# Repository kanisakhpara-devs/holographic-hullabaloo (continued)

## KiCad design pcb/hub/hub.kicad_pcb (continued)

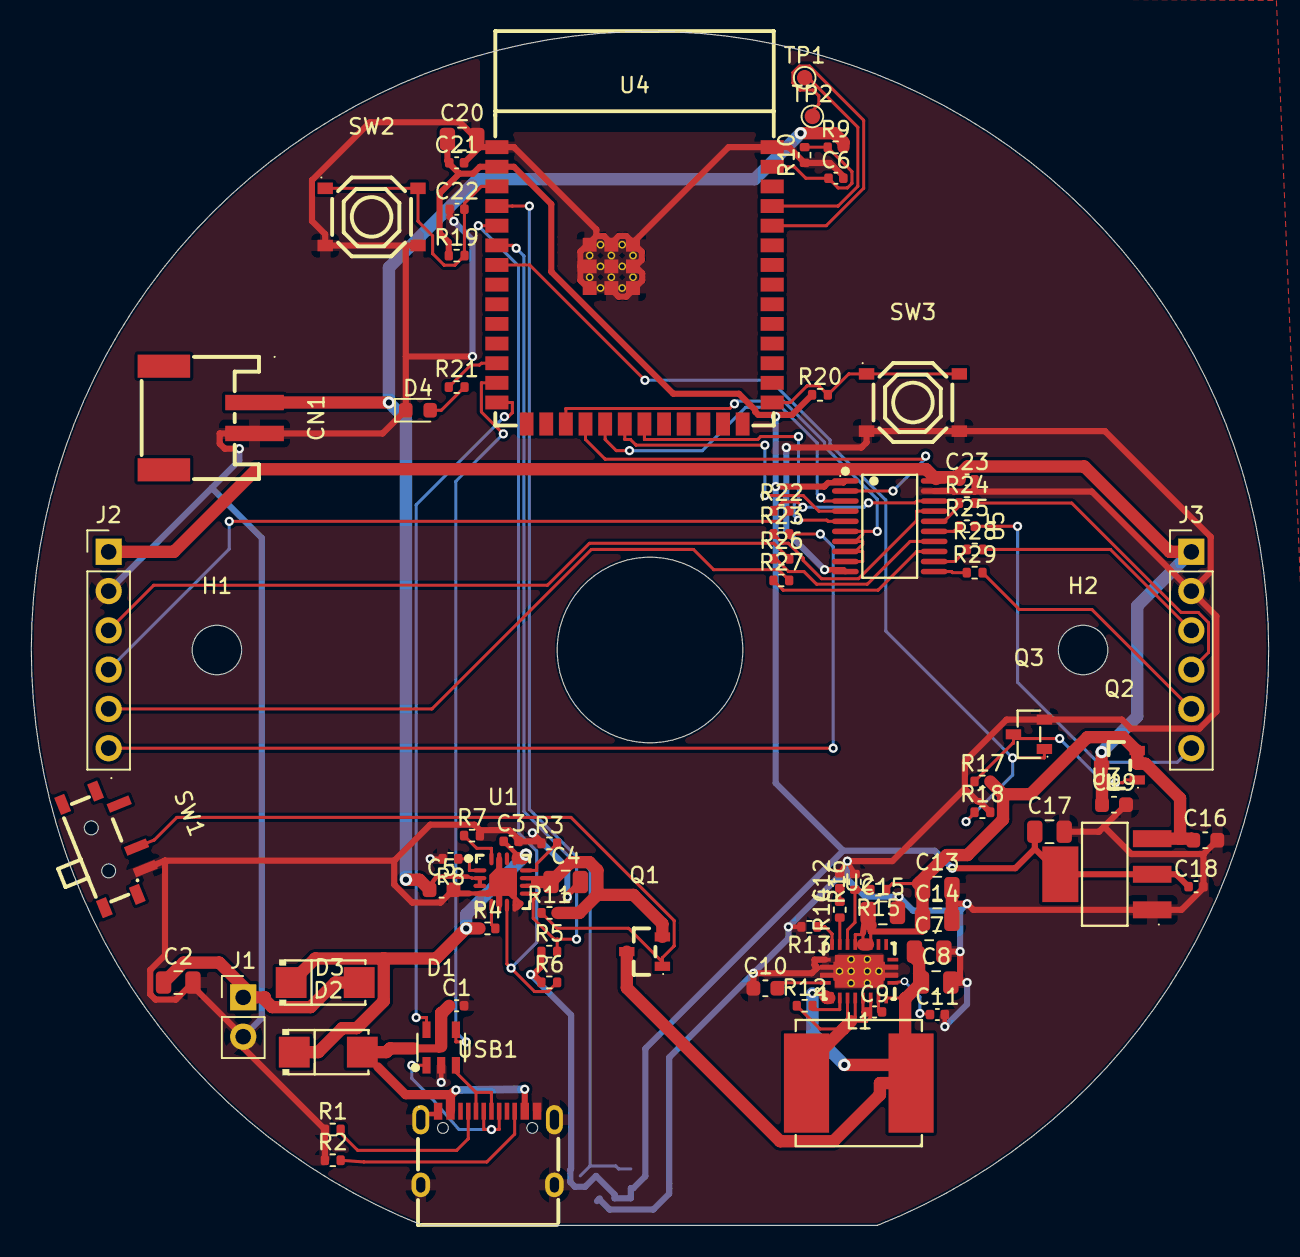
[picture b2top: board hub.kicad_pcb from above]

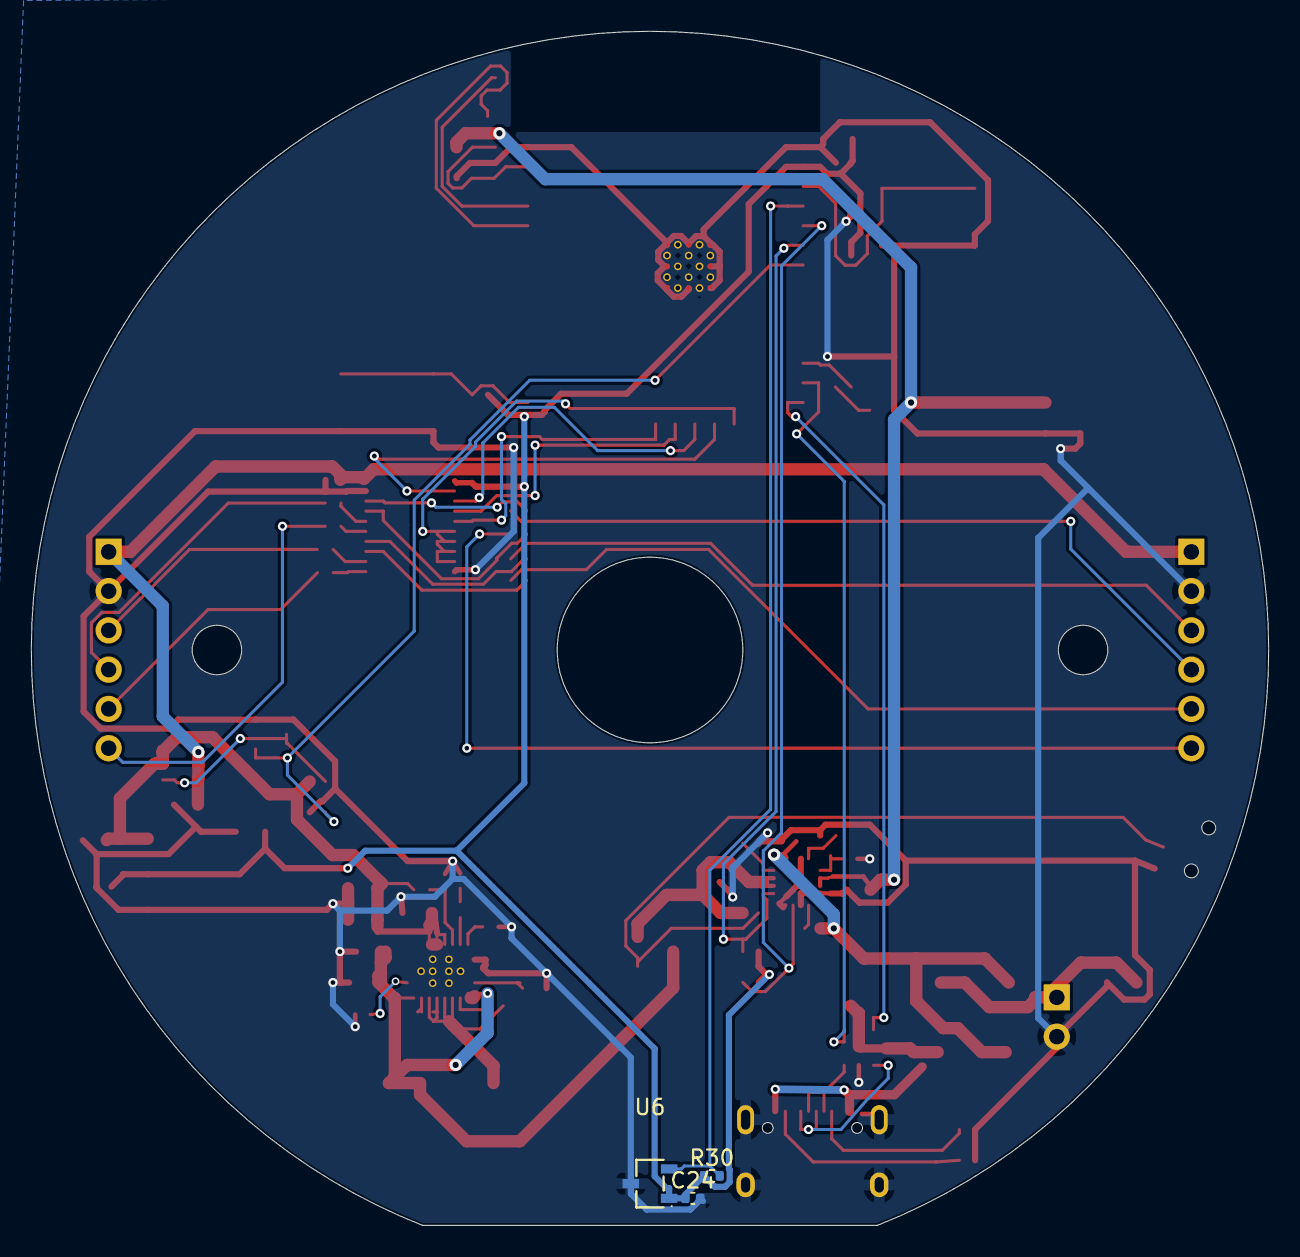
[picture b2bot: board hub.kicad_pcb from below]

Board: 2 copper layers, 80.0 x 77.2 mm, 80 parts (3 on the bottom side), 63 nets.

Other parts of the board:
H1, H2: MountingHole_3.2mm_M3

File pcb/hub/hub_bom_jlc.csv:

"Comment","Designator","Footprint","LCSC Part #"
"100nF","C1,C6,C9,C11,C18,C21,C23,C24","Capacitor_SMD:C_0402_1005Metric","C1525"
"22uF","C2,C4,C7,C8,C13,C14,C15,C17,C20","Capacitor_SMD:C_0805_2012Metric","C45783"
"1uF","C3,C22","Capacitor_SMD:C_0402_1005Metric","C52923"
"10uF","C5,C10,C16,C19","Capacitor_SMD:C_0603_1608Metric","C19702"
"10nF","C12","Capacitor_SMD:C_0402_1005Metric","C15195"
"S2B-PH-SM4-TB","CN1","fallen:CONN-SMD_P2.00_S2B-PH-SM4-TB-LF-SN","C295747"
"USBLC6-2SC6","D1","fallen:SOT-23-6_L2.9-W1.6-P0.95-LS2.8-BL","C7519"
"SS34_C8678","D2,D3","fallen:SMA_L4.3-W2.6-LS5.2-RD","C8678"
"LED","D4","LED_SMD:LED_0603_1608Metric","C2286"
"Conn_01x02","J1","Connector_PinHeader_2.54mm:PinHeader_1x02_P2.54mm_Vertical",""
"Conn_01x06","J2,J3","Connector_PinHeader_2.54mm:PinHeader_1x06_P2.54mm_Vertical",""
"SWPA8040S2R2MT","L1","fallen:IND-SMD_L8.0-W8.0_SWPA8040S","C36415"
"AO3401A","Q1,Q2","fallen:SOT-23_L2.9-W1.3-P1.90-LS2.4-BR","C15127"
"2N7002","Q3","fallen:SOT-23-3_L2.9-W1.3-P1.90-LS2.4-BR","C8545"
"5.1k","R1,R2","Resistor_SMD:R_0402_1005Metric","C25905"
"1.1k","R3","Resistor_SMD:R_0402_1005Metric","C482070"
"100k","R4,R9,R10,R11,R16,R17,R18","Resistor_SMD:R_0402_1005Metric","C25741"
"10k","R5,R6,R8,R14,R19,R20,R30","Resistor_SMD:R_0402_1005Metric","C25744"
"1.18k","R7","Resistor_SMD:R_0402_1005Metric","C2092244"
"330k","R12","Resistor_SMD:R_0402_1005Metric","C102977"
"267k","R13","Resistor_SMD:R_0402_1005Metric","C2998050"
"316k","R15","Resistor_SMD:R_0402_1005Metric","C25777"
"1k","R21","Resistor_SMD:R_0402_1005Metric","C11702"
"33","R22,R23,R24,R25,R26,R27,R28,R29","Resistor_SMD:R_0402_1005Metric","C25105"
"MSK12C02","SW1","fallen:SW-TH_MSK12C02","C431540"
"TS-1187A-B-A-B","SW2,SW3","fallen:SW-SMD_4P-L5.1-W5.1-P3.70-LS6.5-TL_H1.5","C318884"
"TestPoint","TP1,TP2","TestPoint:TestPoint_Pad_D1.0mm",""
"BQ24073RGTR","U1","fallen:QFN-16_L3.0-W3.0-P0.50-TL-EP1.7","C15220"
"TPS61088RHLR","U2","fallen:VQFN-20_L4.6-W3.6-P0.50-BL","C87357"
"AMS1117-3.3","U3","fallen:SOT-223-3_L6.5-W3.4-P2.30-LS7.0-BR","C6186"
"ESP32-S3-WROOM-1-N8","U4","fallen:WIFIM-SMD_ESP32-S3-WROOM-1-N8","C2913198"
"74AHCT245APWJ","U5","fallen:TSSOP-20_L6.5-W4.4-P0.65-LS6.4-BL","C554610"
"DRV5023FAQDBZR","U6","fallen:SOT-23-3_L2.9-W1.6-P1.90-LS2.8-BR","C114983"
"TYPE-C 16PIN 2MD","USB1","fallen:USB-C-SMD_TYPE-C-16PIN-2MD-073","C2765186"

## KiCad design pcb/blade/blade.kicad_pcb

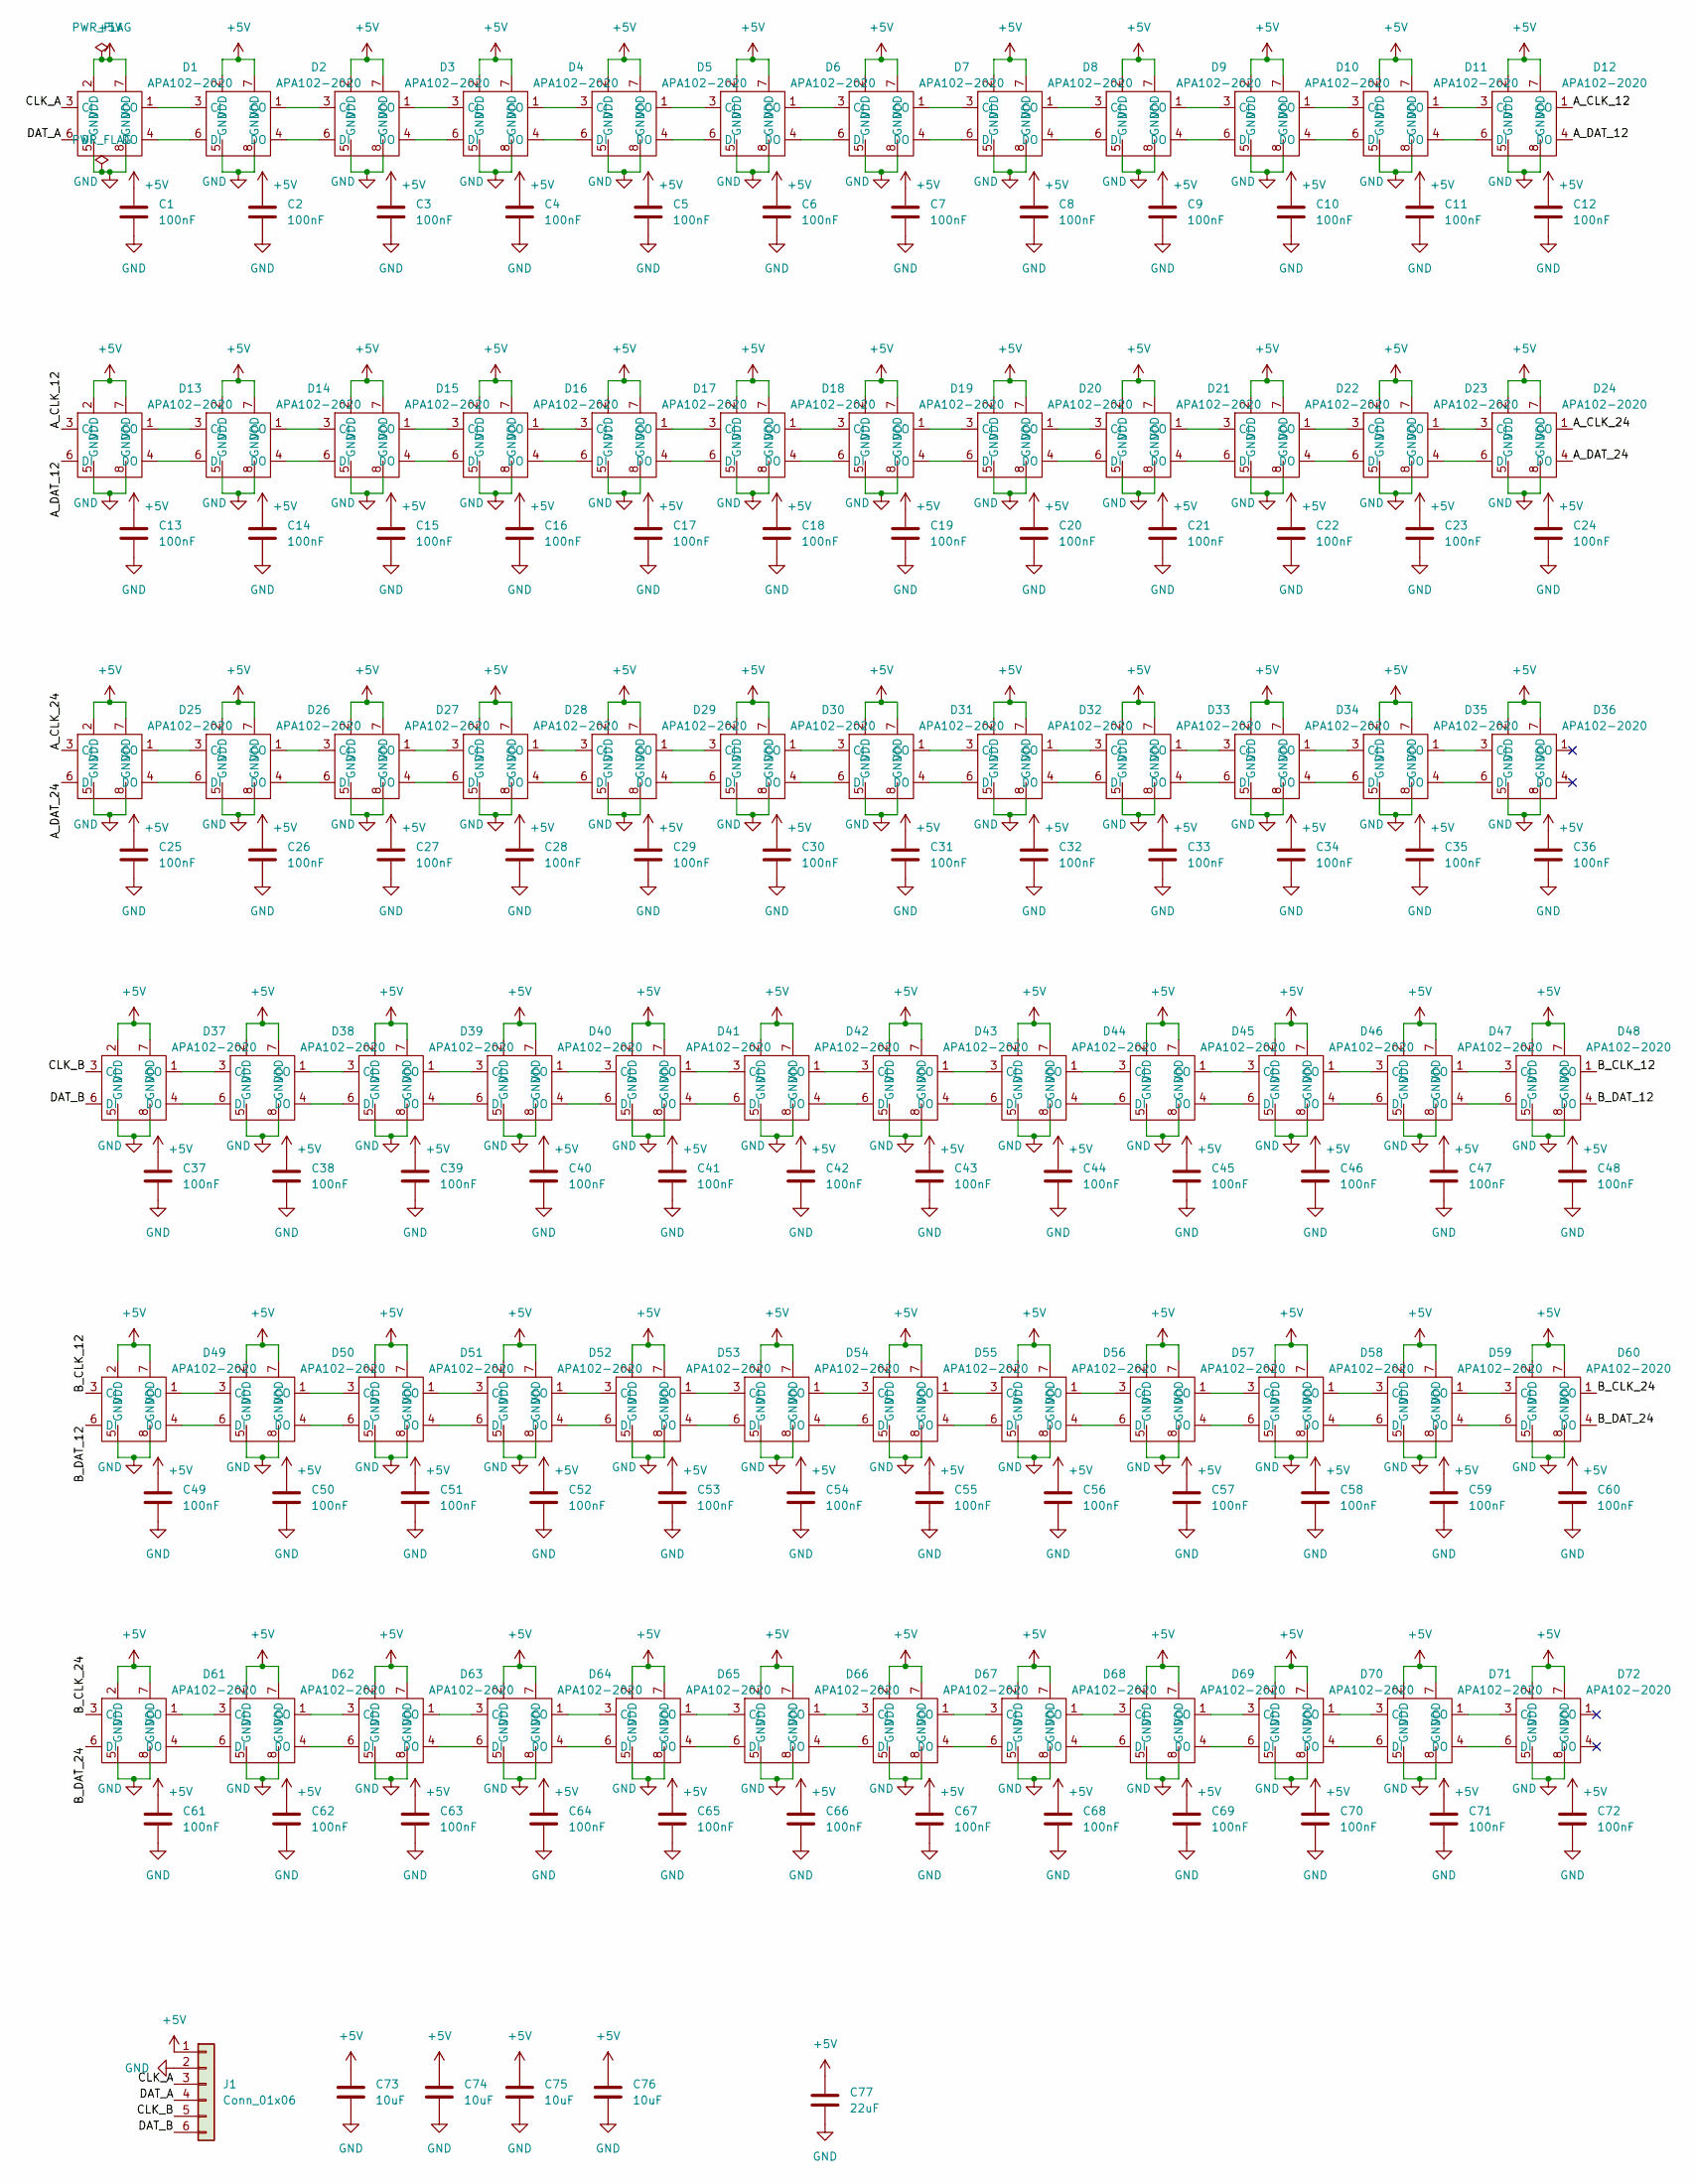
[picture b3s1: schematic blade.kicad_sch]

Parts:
C1, C2, C3, C4, C5, C6, C7, C8, C9, C10, C11, C12, C13, C14, C15, C16, C17, C18, C19, C20, C21, C22, C23, C24, C25, C26, C27, C28, C29, C30, C31, C32, C33, C34, C35, C36, C37, C38, C39, C40, C41, C42, C43, C44, C45, C46, C47, C48, C49, C50, C51, C52, C53, C54, C55, C56, C57, C58, C59, C60, C61, C62, C63, C64, C65, C66, C67, C68, C69, C70, C71, C72: 100nF; C_0402_1005Metric
C73, C74, C75, C76: 10uF; C_0603_1608Metric
C77: 22uF; C_0603_1608Metric
D1, D2, D3, D4, D5, D6, D7, D8, D9, D10, D11, D12, D13, D14, D15, D16, D17, D18, D19, D20, D21, D22, D23, D24, D25, D26, D27, D28, D29, D30, D31, D32, D33, D34, D35, D36, D37, D38, D39, D40, D41, D42, D43, D44, D45, D46, D47, D48, D49, D50, D51, D52, D53, D54, D55, D56, D57, D58, D59, D60, D61, D62, D63, D64, D65, D66, D67, D68, D69, D70, D71, D72: APA102-2020
J1: Conn_01x06; PinHeader_2x03_P2.54mm_Vertical

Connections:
+5V: C1.1, C2.1, C3.1, C4.1, C5.1, C6.1, C7.1, C8.1, C9.1, C10.1, C11.1, C12.1, C13.1, C14.1, C15.1, C16.1, C17.1, C18.1, C19.1, C20.1, C21.1, C22.1, C23.1, C24.1, C25.1, C26.1, C27.1, C28.1, C29.1, C30.1, C31.1, C32.1, C33.1, C34.1, C35.1, C36.1, C37.1, C38.1, C39.1, C40.1, C41.1, C42.1, C43.1, C44.1, C45.1, C46.1, C47.1, C48.1, C49.1, C50.1, C51.1, C52.1, C53.1, C54.1, C55.1, C56.1, C57.1, C58.1, C59.1, C60.1, C61.1, C62.1, C63.1, C64.1, C65.1, C66.1, C67.1, C68.1, C69.1, C70.1, C71.1, C72.1, C73.1, C74.1, C75.1, C76.1, C77.1, D1.2 (VDD), D1.7 (VDD), D2.2 (VDD), D2.7 (VDD), D3.2 (VDD), D3.7 (VDD), D4.2 (VDD), D4.7 (VDD), D5.2 (VDD), D5.7 (VDD), D6.2 (VDD), D6.7 (VDD), D7.2 (VDD), D7.7 (VDD), D8.2 (VDD), D8.7 (VDD), D9.2 (VDD), D9.7 (VDD), D10.2 (VDD), D10.7 (VDD), D11.2 (VDD), D11.7 (VDD), D12.2 (VDD), D12.7 (VDD), D13.2 (VDD), D13.7 (VDD), D14.2 (VDD), D14.7 (VDD), D15.2 (VDD), D15.7 (VDD), D16.2 (VDD), D16.7 (VDD), D17.2 (VDD), D17.7 (VDD), D18.2 (VDD), D18.7 (VDD), D19.2 (VDD), D19.7 (VDD), D20.2 (VDD), D20.7 (VDD), D21.2 (VDD), D21.7 (VDD), D22.2 (VDD), D22.7 (VDD), D23.2 (VDD), D23.7 (VDD), D24.2 (VDD), D24.7 (VDD), D25.2 (VDD), D25.7 (VDD), D26.2 (VDD), D26.7 (VDD), D27.2 (VDD), D27.7 (VDD), D28.2 (VDD), D28.7 (VDD), D29.2 (VDD), D29.7 (VDD), D30.2 (VDD), D30.7 (VDD), D31.2 (VDD), D31.7 (VDD), D32.2 (VDD), D32.7 (VDD), D33.2 (VDD), D33.7 (VDD), D34.2 (VDD), D34.7 (VDD), D35.2 (VDD), D35.7 (VDD), D36.2 (VDD), D36.7 (VDD), D37.2 (VDD), D37.7 (VDD), D38.2 (VDD), D38.7 (VDD), D39.2 (VDD), D39.7 (VDD), D40.2 (VDD), D40.7 (VDD), D41.2 (VDD), D41.7 (VDD), D42.2 (VDD), D42.7 (VDD), D43.2 (VDD), D43.7 (VDD), D44.2 (VDD), D44.7 (VDD), D45.2 (VDD), D45.7 (VDD), D46.2 (VDD), D46.7 (VDD), D47.2 (VDD), D47.7 (VDD), D48.2 (VDD), D48.7 (VDD), D49.2 (VDD), D49.7 (VDD), D50.2 (VDD), D50.7 (VDD), D51.2 (VDD), D51.7 (VDD), D52.2 (VDD), D52.7 (VDD), D53.2 (VDD), D53.7 (VDD), D54.2 (VDD), D54.7 (VDD), D55.2 (VDD), D55.7 (VDD), D56.2 (VDD), D56.7 (VDD), D57.2 (VDD), D57.7 (VDD), D58.2 (VDD), D58.7 (VDD), D59.2 (VDD), D59.7 (VDD), D60.2 (VDD), D60.7 (VDD), D61.2 (VDD), D61.7 (VDD), D62.2 (VDD), D62.7 (VDD), D63.2 (VDD), D63.7 (VDD), D64.2 (VDD), D64.7 (VDD), D65.2 (VDD), D65.7 (VDD), D66.2 (VDD), D66.7 (VDD), D67.2 (VDD), D67.7 (VDD), D68.2 (VDD), D68.7 (VDD), D69.2 (VDD), D69.7 (VDD), D70.2 (VDD), D70.7 (VDD), D71.2 (VDD), D71.7 (VDD), D72.2 (VDD), D72.7 (VDD), J1.1
/A_CLK_12: D12.1 (CO), D13.3 (CI)
/A_CLK_24: D24.1 (CO), D25.3 (CI)
/A_DAT_12: D12.4 (DO), D13.6 (DI)
/A_DAT_24: D24.4 (DO), D25.6 (DI)
/B_CLK_12: D48.1 (CO), D49.3 (CI)
/B_CLK_24: D60.1 (CO), D61.3 (CI)
/B_DAT_12: D48.4 (DO), D49.6 (DI)
/B_DAT_24: D60.4 (DO), D61.6 (DI)
/CLK_A: D1.3 (CI), J1.3
/CLK_B: D37.3 (CI), J1.5
/DAT_A: D1.6 (DI), J1.4
/DAT_B: D37.6 (DI), J1.6
GND: C1.2, C2.2, C3.2, C4.2, C5.2, C6.2, C7.2, C8.2, C9.2, C10.2, C11.2, C12.2, C13.2, C14.2, C15.2, C16.2, C17.2, C18.2, C19.2, C20.2, C21.2, C22.2, C23.2, C24.2, C25.2, C26.2, C27.2, C28.2, C29.2, C30.2, C31.2, C32.2, C33.2, C34.2, C35.2, C36.2, C37.2, C38.2, C39.2, C40.2, C41.2, C42.2, C43.2, C44.2, C45.2, C46.2, C47.2, C48.2, C49.2, C50.2, C51.2, C52.2, C53.2, C54.2, C55.2, C56.2, C57.2, C58.2, C59.2, C60.2, C61.2, C62.2, C63.2, C64.2, C65.2, C66.2, C67.2, C68.2, C69.2, C70.2, C71.2, C72.2, C73.2, C74.2, C75.2, C76.2, C77.2, D1.5 (GND), D1.8 (GND), D2.5 (GND), D2.8 (GND), D3.5 (GND), D3.8 (GND), D4.5 (GND), D4.8 (GND), D5.5 (GND), D5.8 (GND), D6.5 (GND), D6.8 (GND), D7.5 (GND), D7.8 (GND), D8.5 (GND), D8.8 (GND), D9.5 (GND), D9.8 (GND), D10.5 (GND), D10.8 (GND), D11.5 (GND), D11.8 (GND), D12.5 (GND), D12.8 (GND), D13.5 (GND), D13.8 (GND), D14.5 (GND), D14.8 (GND), D15.5 (GND), D15.8 (GND), D16.5 (GND), D16.8 (GND), D17.5 (GND), D17.8 (GND), D18.5 (GND), D18.8 (GND), D19.5 (GND), D19.8 (GND), D20.5 (GND), D20.8 (GND), D21.5 (GND), D21.8 (GND), D22.5 (GND), D22.8 (GND), D23.5 (GND), D23.8 (GND), D24.5 (GND), D24.8 (GND), D25.5 (GND), D25.8 (GND), D26.5 (GND), D26.8 (GND), D27.5 (GND), D27.8 (GND), D28.5 (GND), D28.8 (GND), D29.5 (GND), D29.8 (GND), D30.5 (GND), D30.8 (GND), D31.5 (GND), D31.8 (GND), D32.5 (GND), D32.8 (GND), D33.5 (GND), D33.8 (GND), D34.5 (GND), D34.8 (GND), D35.5 (GND), D35.8 (GND), D36.5 (GND), D36.8 (GND), D37.5 (GND), D37.8 (GND), D38.5 (GND), D38.8 (GND), D39.5 (GND), D39.8 (GND), D40.5 (GND), D40.8 (GND), D41.5 (GND), D41.8 (GND), D42.5 (GND), D42.8 (GND), D43.5 (GND), D43.8 (GND), D44.5 (GND), D44.8 (GND), D45.5 (GND), D45.8 (GND), D46.5 (GND), D46.8 (GND), D47.5 (GND), D47.8 (GND), D48.5 (GND), D48.8 (GND), D49.5 (GND), D49.8 (GND), D50.5 (GND), D50.8 (GND), D51.5 (GND), D51.8 (GND), D52.5 (GND), D52.8 (GND), D53.5 (GND), D53.8 (GND), D54.5 (GND), D54.8 (GND), D55.5 (GND), D55.8 (GND), D56.5 (GND), D56.8 (GND), D57.5 (GND), D57.8 (GND), D58.5 (GND), D58.8 (GND), D59.5 (GND), D59.8 (GND), D60.5 (GND), D60.8 (GND), D61.5 (GND), D61.8 (GND), D62.5 (GND), D62.8 (GND), D63.5 (GND), D63.8 (GND), D64.5 (GND), D64.8 (GND), D65.5 (GND), D65.8 (GND), D66.5 (GND), D66.8 (GND), D67.5 (GND), D67.8 (GND), D68.5 (GND), D68.8 (GND), D69.5 (GND), D69.8 (GND), D70.5 (GND), D70.8 (GND), D71.5 (GND), D71.8 (GND), D72.5 (GND), D72.8 (GND), J1.2
unnamed: D1.1 (CO), D2.3 (CI)
unnamed: D1.4 (DO), D2.6 (DI)
unnamed: D2.1 (CO), D3.3 (CI)
unnamed: D2.4 (DO), D3.6 (DI)
unnamed: D3.1 (CO), D4.3 (CI)
unnamed: D3.4 (DO), D4.6 (DI)
unnamed: D4.1 (CO), D5.3 (CI)
unnamed: D4.4 (DO), D5.6 (DI)
unnamed: D5.1 (CO), D6.3 (CI)
unnamed: D5.4 (DO), D6.6 (DI)
unnamed: D6.1 (CO), D7.3 (CI)
unnamed: D6.4 (DO), D7.6 (DI)
unnamed: D7.1 (CO), D8.3 (CI)
unnamed: D7.4 (DO), D8.6 (DI)
unnamed: D8.1 (CO), D9.3 (CI)
unnamed: D8.4 (DO), D9.6 (DI)
unnamed: D9.1 (CO), D10.3 (CI)
unnamed: D10.1 (CO), D11.3 (CI)
unnamed: D9.4 (DO), D10.6 (DI)
unnamed: D10.4 (DO), D11.6 (DI)
unnamed: D11.1 (CO), D12.3 (CI)
unnamed: D11.4 (DO), D12.6 (DI)
unnamed: D13.1 (CO), D14.3 (CI)
unnamed: D13.4 (DO), D14.6 (DI)
unnamed: D14.1 (CO), D15.3 (CI)
unnamed: D14.4 (DO), D15.6 (DI)
unnamed: D15.1 (CO), D16.3 (CI)
unnamed: D15.4 (DO), D16.6 (DI)
unnamed: D16.1 (CO), D17.3 (CI)
unnamed: D16.4 (DO), D17.6 (DI)
unnamed: D17.1 (CO), D18.3 (CI)
unnamed: D17.4 (DO), D18.6 (DI)
unnamed: D18.1 (CO), D19.3 (CI)
unnamed: D18.4 (DO), D19.6 (DI)
unnamed: D19.1 (CO), D20.3 (CI)
unnamed: D19.4 (DO), D20.6 (DI)
unnamed: D20.1 (CO), D21.3 (CI)
unnamed: D20.4 (DO), D21.6 (DI)
unnamed: D21.1 (CO), D22.3 (CI)
unnamed: D21.4 (DO), D22.6 (DI)
unnamed: D22.1 (CO), D23.3 (CI)
unnamed: D22.4 (DO), D23.6 (DI)
unnamed: D23.1 (CO), D24.3 (CI)
unnamed: D23.4 (DO), D24.6 (DI)
unnamed: D25.1 (CO), D26.3 (CI)
unnamed: D25.4 (DO), D26.6 (DI)
unnamed: D26.1 (CO), D27.3 (CI)
unnamed: D26.4 (DO), D27.6 (DI)
unnamed: D27.1 (CO), D28.3 (CI)
unnamed: D27.4 (DO), D28.6 (DI)
unnamed: D28.1 (CO), D29.3 (CI)
unnamed: D28.4 (DO), D29.6 (DI)
unnamed: D29.1 (CO), D30.3 (CI)
unnamed: D29.4 (DO), D30.6 (DI)
unnamed: D30.1 (CO), D31.3 (CI)
unnamed: D30.4 (DO), D31.6 (DI)
unnamed: D31.1 (CO), D32.3 (CI)
unnamed: D31.4 (DO), D32.6 (DI)
unnamed: D32.1 (CO), D33.3 (CI)
unnamed: D32.4 (DO), D33.6 (DI)
unnamed: D33.1 (CO), D34.3 (CI)
unnamed: D33.4 (DO), D34.6 (DI)
unnamed: D34.1 (CO), D35.3 (CI)
unnamed: D34.4 (DO), D35.6 (DI)
unnamed: D35.1 (CO), D36.3 (CI)
unnamed: D35.4 (DO), D36.6 (DI)
unnamed: D37.1 (CO), D38.3 (CI)
unnamed: D37.4 (DO), D38.6 (DI)
unnamed: D38.1 (CO), D39.3 (CI)
unnamed: D38.4 (DO), D39.6 (DI)
unnamed: D39.1 (CO), D40.3 (CI)
unnamed: D39.4 (DO), D40.6 (DI)
unnamed: D40.1 (CO), D41.3 (CI)
unnamed: D40.4 (DO), D41.6 (DI)
unnamed: D41.1 (CO), D42.3 (CI)
unnamed: D41.4 (DO), D42.6 (DI)
unnamed: D42.1 (CO), D43.3 (CI)
unnamed: D42.4 (DO), D43.6 (DI)
unnamed: D43.1 (CO), D44.3 (CI)
unnamed: D43.4 (DO), D44.6 (DI)
unnamed: D44.1 (CO), D45.3 (CI)
unnamed: D44.4 (DO), D45.6 (DI)
unnamed: D45.1 (CO), D46.3 (CI)
unnamed: D45.4 (DO), D46.6 (DI)
unnamed: D46.1 (CO), D47.3 (CI)
unnamed: D46.4 (DO), D47.6 (DI)
unnamed: D47.1 (CO), D48.3 (CI)
unnamed: D47.4 (DO), D48.6 (DI)
unnamed: D49.1 (CO), D50.3 (CI)
unnamed: D49.4 (DO), D50.6 (DI)
unnamed: D50.1 (CO), D51.3 (CI)
unnamed: D50.4 (DO), D51.6 (DI)
unnamed: D51.1 (CO), D52.3 (CI)
unnamed: D51.4 (DO), D52.6 (DI)
unnamed: D52.1 (CO), D53.3 (CI)
unnamed: D52.4 (DO), D53.6 (DI)
unnamed: D53.1 (CO), D54.3 (CI)
unnamed: D53.4 (DO), D54.6 (DI)
unnamed: D54.1 (CO), D55.3 (CI)
unnamed: D54.4 (DO), D55.6 (DI)
unnamed: D55.1 (CO), D56.3 (CI)
unnamed: D55.4 (DO), D56.6 (DI)
unnamed: D56.1 (CO), D57.3 (CI)
unnamed: D56.4 (DO), D57.6 (DI)
unnamed: D57.1 (CO), D58.3 (CI)
unnamed: D57.4 (DO), D58.6 (DI)
unnamed: D58.1 (CO), D59.3 (CI)
unnamed: D58.4 (DO), D59.6 (DI)
unnamed: D59.1 (CO), D60.3 (CI)
unnamed: D59.4 (DO), D60.6 (DI)
unnamed: D61.1 (CO), D62.3 (CI)
unnamed: D61.4 (DO), D62.6 (DI)
unnamed: D62.1 (CO), D63.3 (CI)
unnamed: D62.4 (DO), D63.6 (DI)
unnamed: D63.1 (CO), D64.3 (CI)
unnamed: D63.4 (DO), D64.6 (DI)
unnamed: D64.1 (CO), D65.3 (CI)
unnamed: D64.4 (DO), D65.6 (DI)
unnamed: D65.1 (CO), D66.3 (CI)
unnamed: D65.4 (DO), D66.6 (DI)
unnamed: D66.1 (CO), D67.3 (CI)
unnamed: D66.4 (DO), D67.6 (DI)
unnamed: D67.1 (CO), D68.3 (CI)
unnamed: D67.4 (DO), D68.6 (DI)
unnamed: D68.1 (CO), D69.3 (CI)
unnamed: D68.4 (DO), D69.6 (DI)
unnamed: D69.1 (CO), D70.3 (CI)
unnamed: D69.4 (DO), D70.6 (DI)
unnamed: D70.1 (CO), D71.3 (CI)
unnamed: D70.4 (DO), D71.6 (DI)
unnamed: D71.1 (CO), D72.3 (CI)
unnamed: D71.4 (DO), D72.6 (DI)

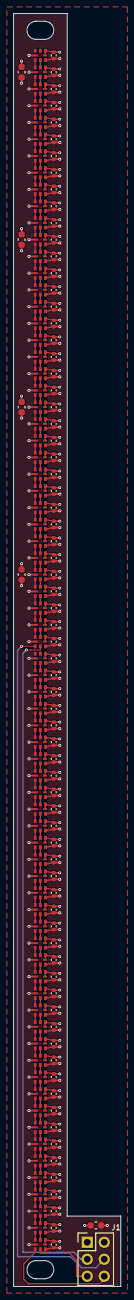
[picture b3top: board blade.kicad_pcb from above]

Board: 4 copper layers, 16.0 x 190.0 mm, 150 parts (0 on the bottom side), 146 nets.

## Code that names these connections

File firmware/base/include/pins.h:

// Base pin map for the custom ESP32-S3-WROOM-1-N8 base board (pcb/base, Nov 19 revision).
// Matches the base pin map in the README (firmware section) and pcb/base/base.kicad_sch. Keep in sync with the schematic.
// Avoid strapping pins (IO0, IO3, IO45, IO46) and the USB pins (IO19, IO20).
#pragma once

// Motor (AO4406A low-side MOSFET, 33R gate + 100k pull-down, 20 kHz PWM)
#define PIN_MOTOR_PWM     4

// Talk button (to GND, internal pull-up, active low)
#define PIN_TALK_BUTTON   5

// VL53L0X distance sensors (front and back). XSHUT lines give each sensor its own I2C address.
#define PIN_TOF1_XSHUT    6   // front sensor
#define PIN_TOF2_XSHUT    7   // back sensor
#define PIN_I2C_SDA       8   // VL53L0X x2
#define PIN_I2C_SCL       9

// MAX98357A speaker amp (I2S out). SD_MODE tied through 1M to this pin (mono).
#define PIN_AMP_BCLK      12
#define PIN_AMP_LRC       13
#define PIN_AMP_DIN       14
#define PIN_AMP_EN        15

// INMP441 mic (I2S in)
#define PIN_MIC_SCK       16
#define PIN_MIC_WS        17
#define PIN_MIC_SD        18

// Status LED
#define PIN_STATUS_LED    21

// USB (native USB: USB audio + CDC serial to the laptop). Do not reuse.
#define PIN_USB_DN        19
#define PIN_USB_DP        20
